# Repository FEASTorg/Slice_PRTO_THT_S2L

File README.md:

# Prototyping Slice

THT components.

BREAD slice for creating new BREAD slices.

## Introduction

[Short introduction on the project.]

## Usage

[Explain how to use the project. Include examples and screenshots if applicable.]

## Documentation

Please refer to the [docs](/docs) for more info.

---

<div align="center">
  
</div>

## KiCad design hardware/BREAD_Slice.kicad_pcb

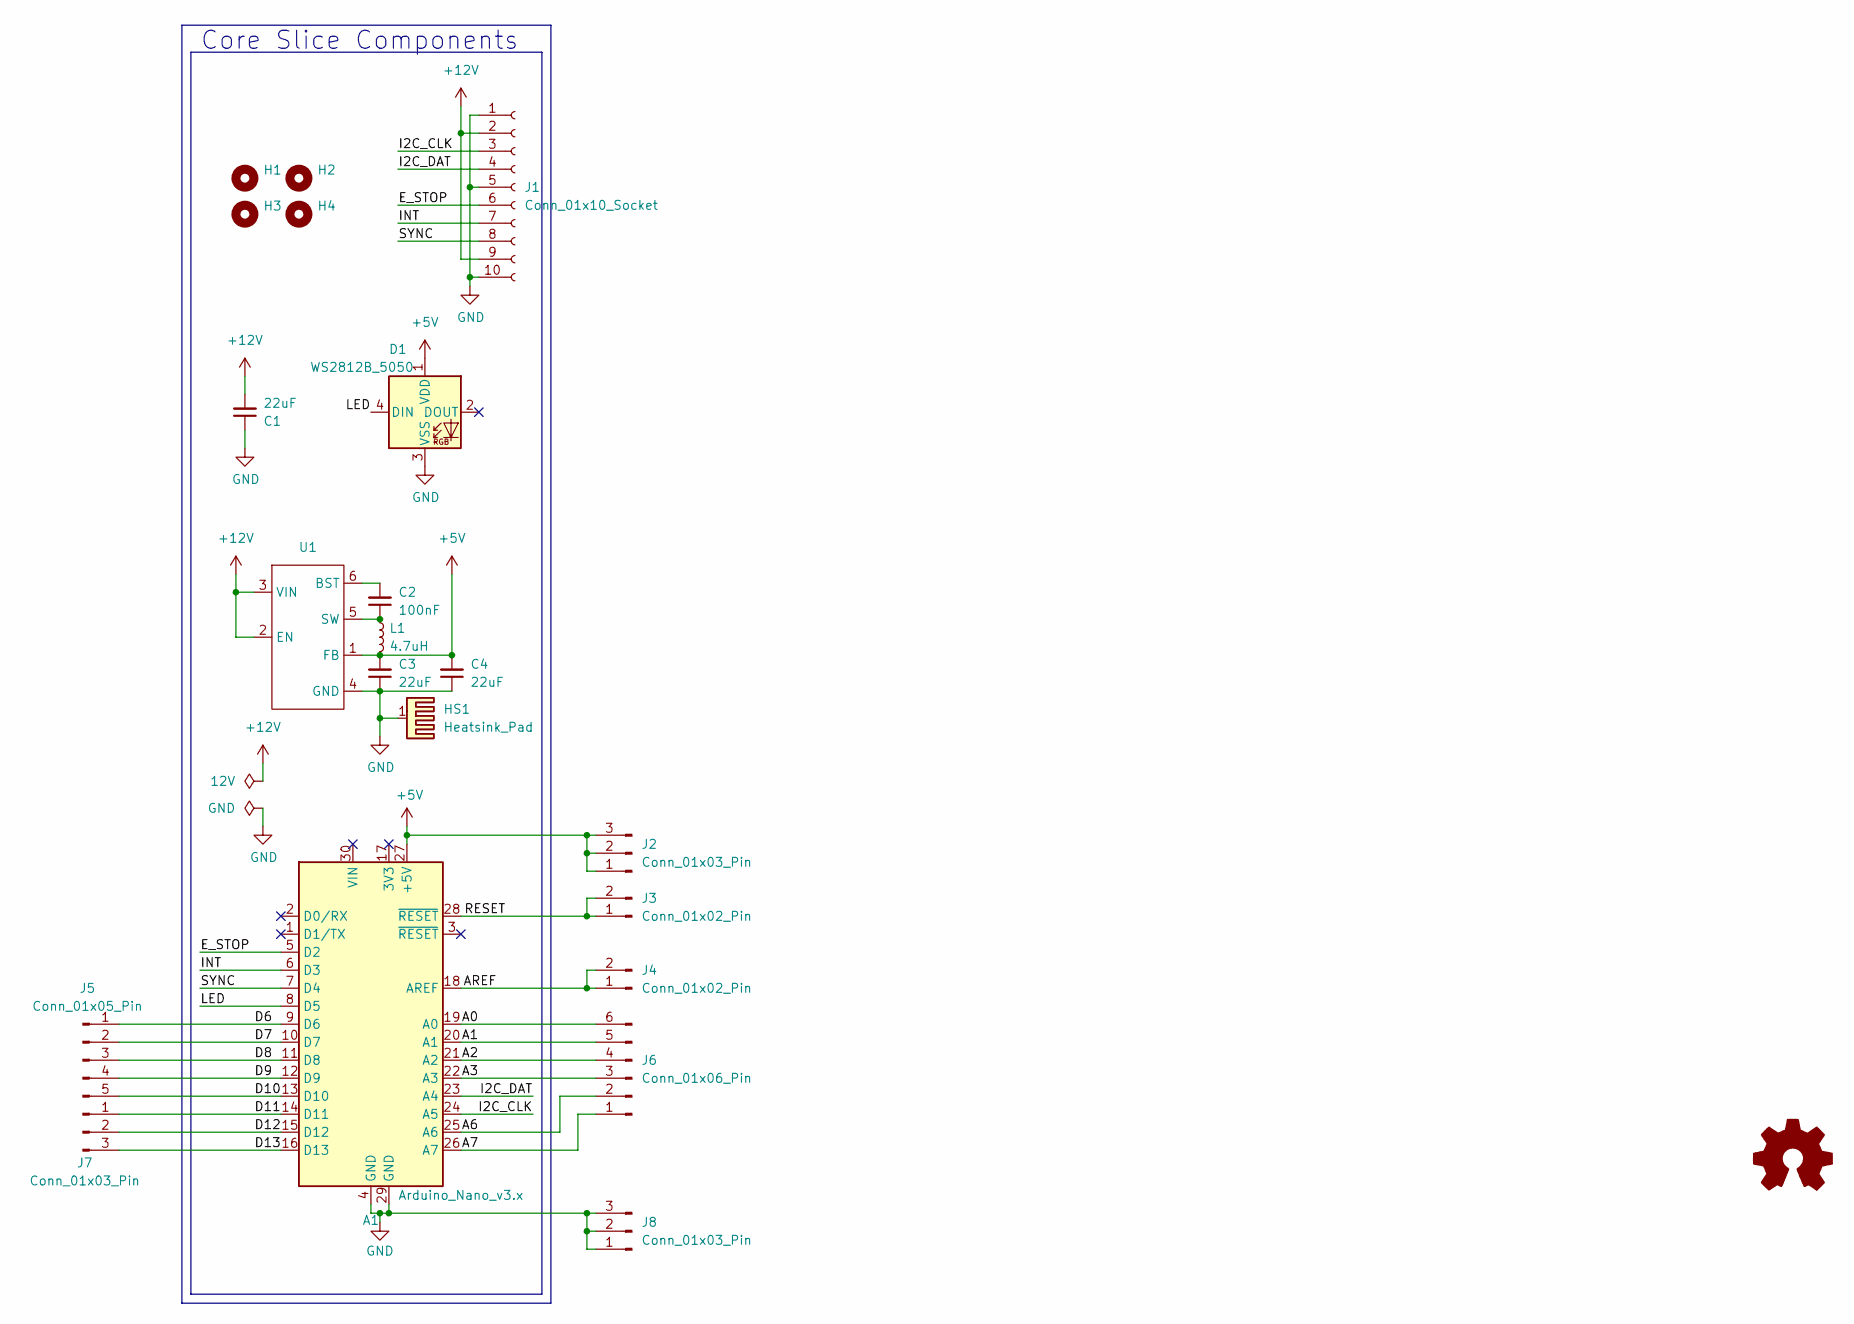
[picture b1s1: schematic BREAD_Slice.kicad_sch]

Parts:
A1: Arduino_Nano_v3.x; Arduino_Nano
C1, C3, C4: 22uF; C_1206_3216Metric
C2: 100nF; C_1206_3216Metric
D1: WS2812B_5050; WS2812-5050-4PIN
H1, H2, H3, H4: MountingHole; MountingHole_5mm
HS1: Heatsink_Pad; Thermal_Pad
J1: Conn_01x10_Socket; PinSocket_1x10_P2.54mm_Horizontal
J2, J7, J8: Conn_01x03_Pin; PinHeader_1x03_P2.54mm_Vertical
J3, J4: Conn_01x02_Pin; PinHeader_1x02_P2.54mm_Vertical
J5: Conn_01x05_Pin; PinHeader_1x05_P2.54mm_Vertical
J6: Conn_01x06_Pin; PinHeader_1x06_P2.54mm_Vertical
L1: 4.7uH; L_1210_3225Metric
U1: TSOT-23-6

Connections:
+5V: A1.27 (+5V), C3.2, C4.2, D1.1 (VDD), J2.1, J2.2, J2.3, L1.2, U1.1 (FB)
+12V: C1.2, J1.2, J1.9, U1.2 (EN), U1.3 (VIN)
/A0: A1.19 (A0), J6.6
/A1: A1.20 (A1), J6.5
/A2: A1.21 (A2), J6.4
/A3: A1.22 (A3), J6.3
/A6: A1.25 (A6), J6.2
/A7: A1.26 (A7), J6.1
/AREF: A1.18 (AREF), J4.1, J4.2
/D6: A1.9 (D6), J5.1
/D7: A1.10 (D7), J5.2
/D8: A1.11 (D8), J5.3
/D9: A1.12 (D9), J5.4
/D10: A1.13 (D10), J5.5
/D11: A1.14 (D11), J7.1
/D12: A1.15 (D12), J7.2
/D13: A1.16 (D13), J7.3
/E_STOP: A1.5 (D2), J1.6
/I2C_CLK: A1.24 (A5), J1.3
/I2C_DAT: A1.23 (A4), J1.4
/INT: A1.6 (D3), J1.7
/LED: A1.8 (D5), D1.4 (DIN)
/RESET: A1.28 (~RESET), J3.1, J3.2
/SYNC: A1.7 (D4), J1.8
GND: A1.4 (GND), A1.29 (GND), C1.1, C3.1, C4.1, D1.3 (VSS), HS1.1, J1.1, J1.5, J1.10, J8.1, J8.2, J8.3, U1.4 (GND)
unnamed: C2.2, U1.6 (BST)
unnamed: C2.1, L1.1, U1.5 (SW)

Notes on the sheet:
Core Slice Components

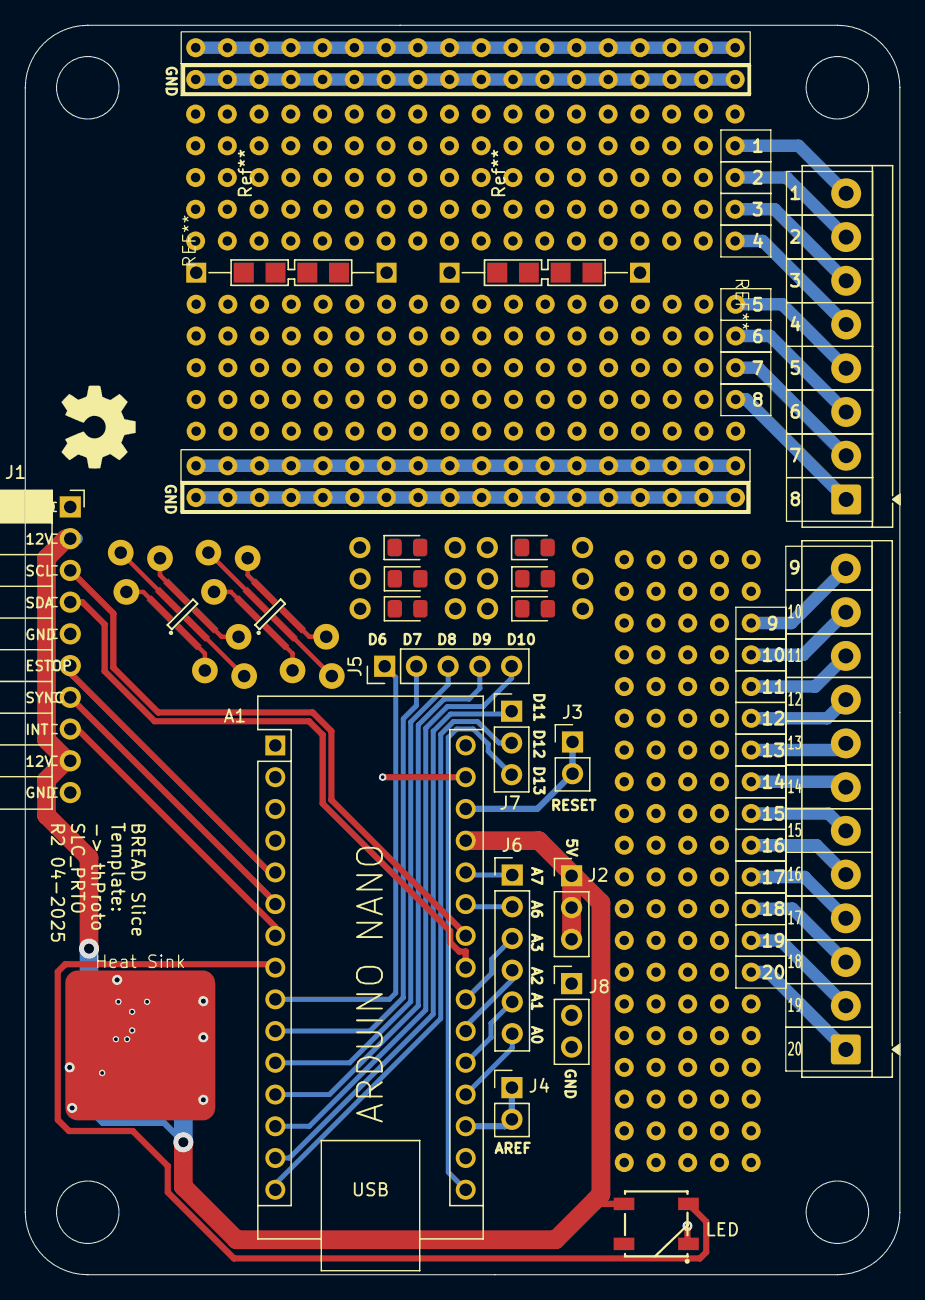
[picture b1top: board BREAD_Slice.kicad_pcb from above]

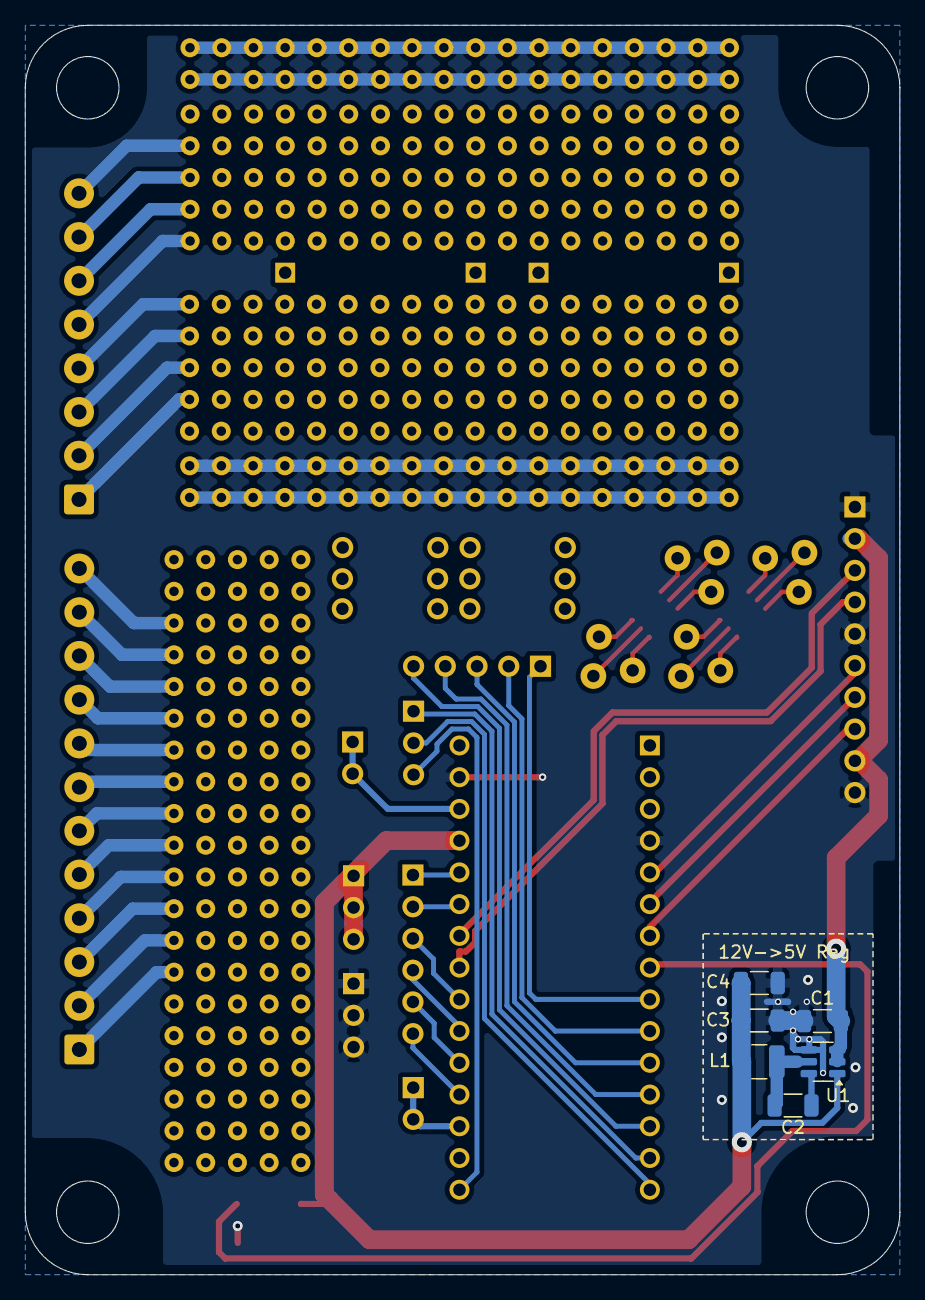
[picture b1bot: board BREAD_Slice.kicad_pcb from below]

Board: 2 copper layers, 70.0 x 100.0 mm, 24 parts (6 on the bottom side), 27 nets.

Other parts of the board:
Logo1: Logo_Open_Hardware_Small; OSHW-Symbol_6.7x6mm_SilkScreen
Ref**: Val**; 1206_HandSolder_Dual_TH_AnnularPad
Ref**#2: Val**; 1206_HandSolder_Dual_TH_AnnularPad

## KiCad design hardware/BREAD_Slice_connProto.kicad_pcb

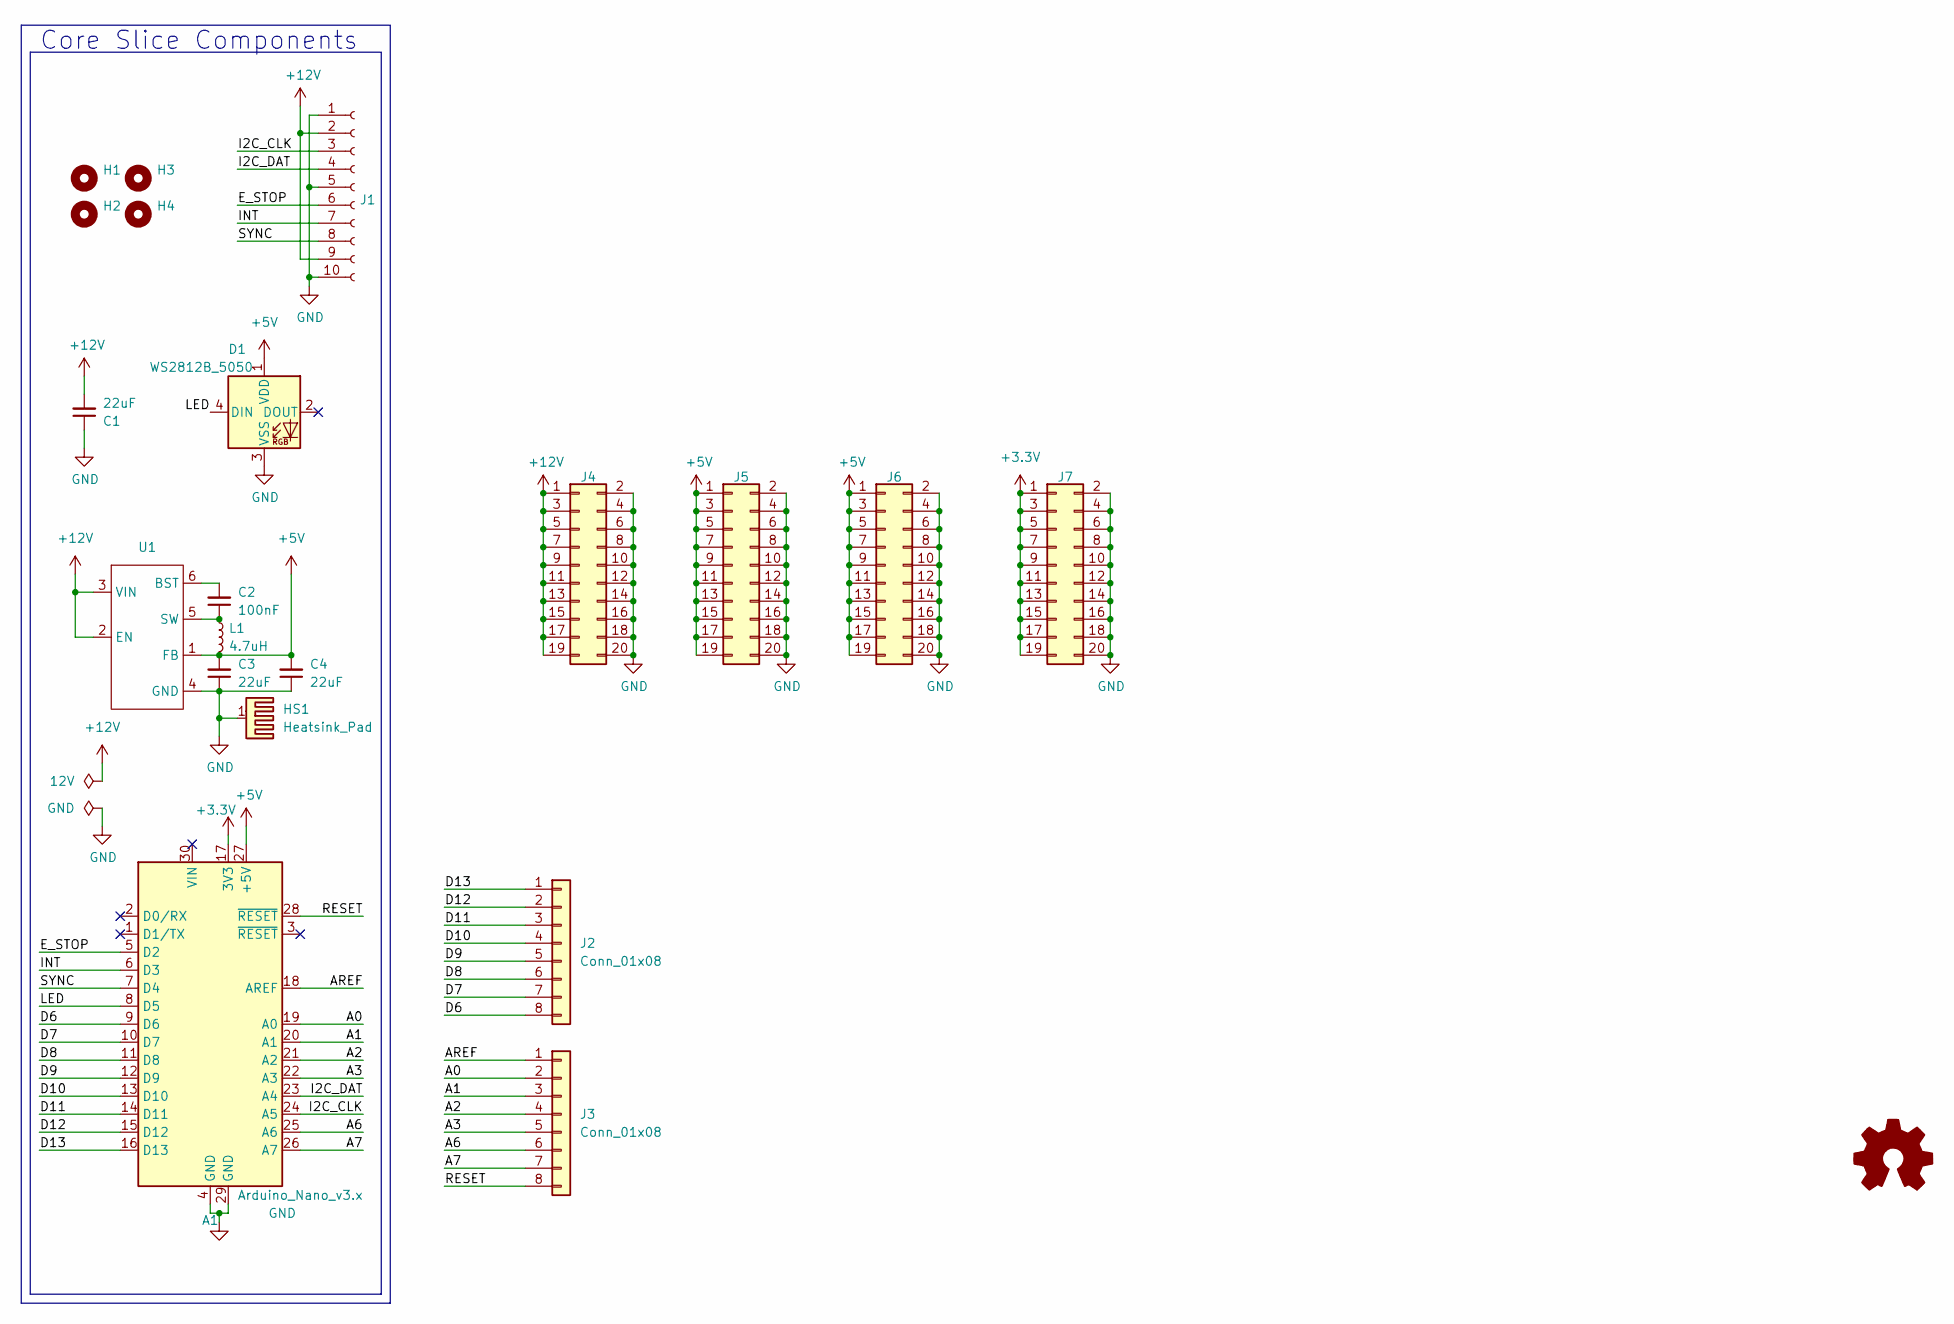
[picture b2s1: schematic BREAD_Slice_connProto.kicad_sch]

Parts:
A1: Arduino_Nano_v3.x; Arduino_Nano
C1, C3, C4: 22uF; C_1206_3216Metric
C2: 100nF; C_1206_3216Metric
D1: WS2812B_5050; WS2812-5050-4PIN
H1, H2, H3, H4: MountingHole; MountingHole_5mm
HS1: Heatsink_Pad; Thermal Pad
J1: Conn_01x10_Female; PinSocket_1x10_P2.54mm_Horizontal
J2, J3: Conn_01x08; TerminalBlock_4Ucon_1x08_P3.50mm_Horizontal
J4, J5, J6, J7: Conn_02x10_Odd_Even; PinHeader_2x10_P2.54mm_Vertical
L1: 4.7uH; L_1210_3225Metric
U1: TSOT-23-6

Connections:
+3.3V: A1.17 (3V3), J7.1, J7.3, J7.5, J7.7, J7.9, J7.11, J7.13, J7.15, J7.17, J7.19
+5V: A1.27 (+5V), C3.2, C4.2, D1.1 (VDD), J5.1, J5.3, J5.5, J5.7, J5.9, J5.11, J5.13, J5.15, J5.17, J5.19, J6.1, J6.3, J6.5, J6.7, J6.9, J6.11, J6.13, J6.15, J6.17, J6.19, L1.2, U1.1 (FB)
+12V: C1.2, J1.2, J1.9, J4.1, J4.3, J4.5, J4.7, J4.9, J4.11, J4.13, J4.15, J4.17, J4.19, U1.2 (EN), U1.3 (VIN)
/A0: A1.19 (A0), J3.2
/A1: A1.20 (A1), J3.3
/A2: A1.21 (A2), J3.4
/A3: A1.22 (A3), J3.5
/A6: A1.25 (A6), J3.6
/A7: A1.26 (A7), J3.7
/AREF: A1.18 (AREF), J3.1
/D6: A1.9 (D6), J2.8
/D7: A1.10 (D7), J2.7
/D8: A1.11 (D8), J2.6
/D9: A1.12 (D9), J2.5
/D10: A1.13 (D10), J2.4
/D11: A1.14 (D11), J2.3
/D12: A1.15 (D12), J2.2
/D13: A1.16 (D13), J2.1
/E_STOP: A1.5 (D2), J1.6
/I2C_CLK: A1.24 (A5), J1.3
/I2C_DAT: A1.23 (A4), J1.4
/INT: A1.6 (D3), J1.7
/LED: A1.8 (D5), D1.4 (DIN)
/RESET: A1.28 (~RESET), J3.8
/SYNC: A1.7 (D4), J1.8
GND: A1.4 (GND), A1.29 (GND), C1.1, C3.1, C4.1, D1.3 (VSS), HS1.1, J1.1, J1.5, J1.10, J4.2, J4.4, J4.6, J4.8, J4.10, J4.12, J4.14, J4.16, J4.18, J4.20, J5.2, J5.4, J5.6, J5.8, J5.10, J5.12, J5.14, J5.16, J5.18, J5.20, J6.2, J6.4, J6.6, J6.8, J6.10, J6.12, J6.14, J6.16, J6.18, J6.20, J7.2, J7.4, J7.6, J7.8, J7.10, J7.12, J7.14, J7.16, J7.18, J7.20, U1.4 (GND)
unnamed: C2.2, U1.6 (BST)
unnamed: C2.1, L1.1, U1.5 (SW)

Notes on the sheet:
Core Slice Components

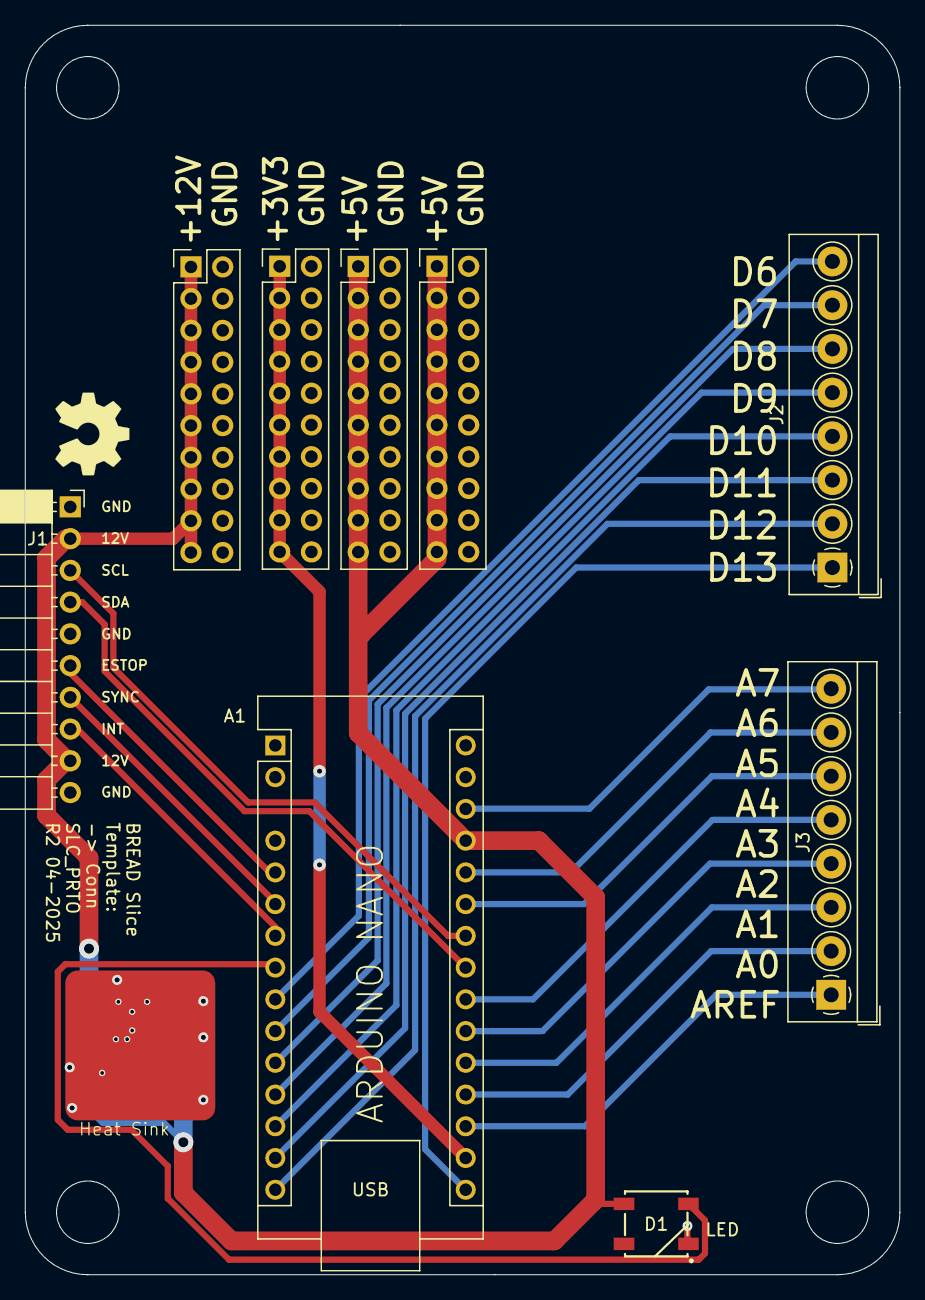
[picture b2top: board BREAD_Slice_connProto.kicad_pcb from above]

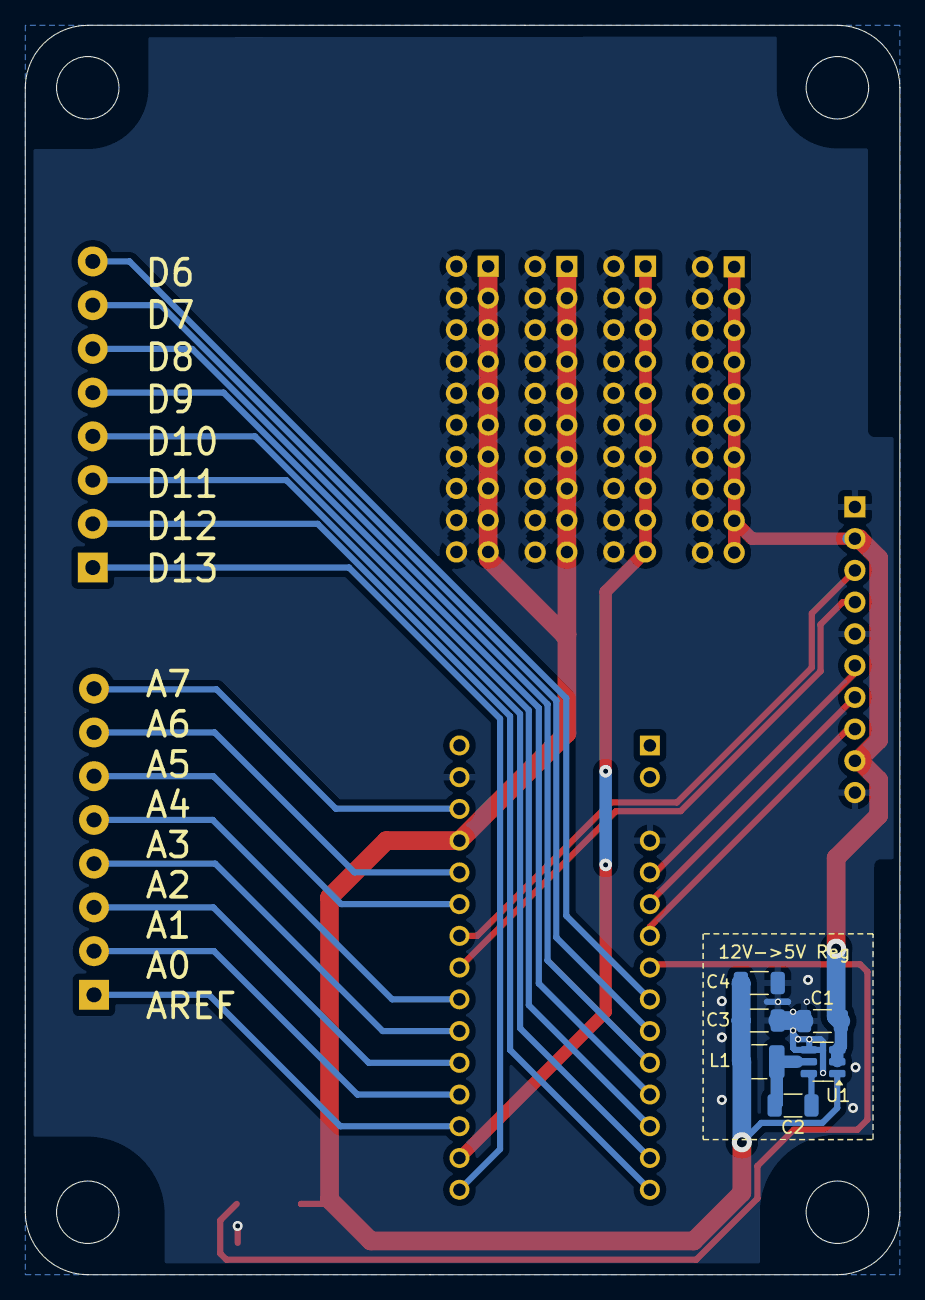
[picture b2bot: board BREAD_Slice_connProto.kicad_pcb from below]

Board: 2 copper layers, 70.0 x 100.0 mm, 21 parts (6 on the bottom side), 28 nets.

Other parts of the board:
Logo1: Logo_Open_Hardware_Small; OSHW-Symbol_6.7x6mm_SilkScreen

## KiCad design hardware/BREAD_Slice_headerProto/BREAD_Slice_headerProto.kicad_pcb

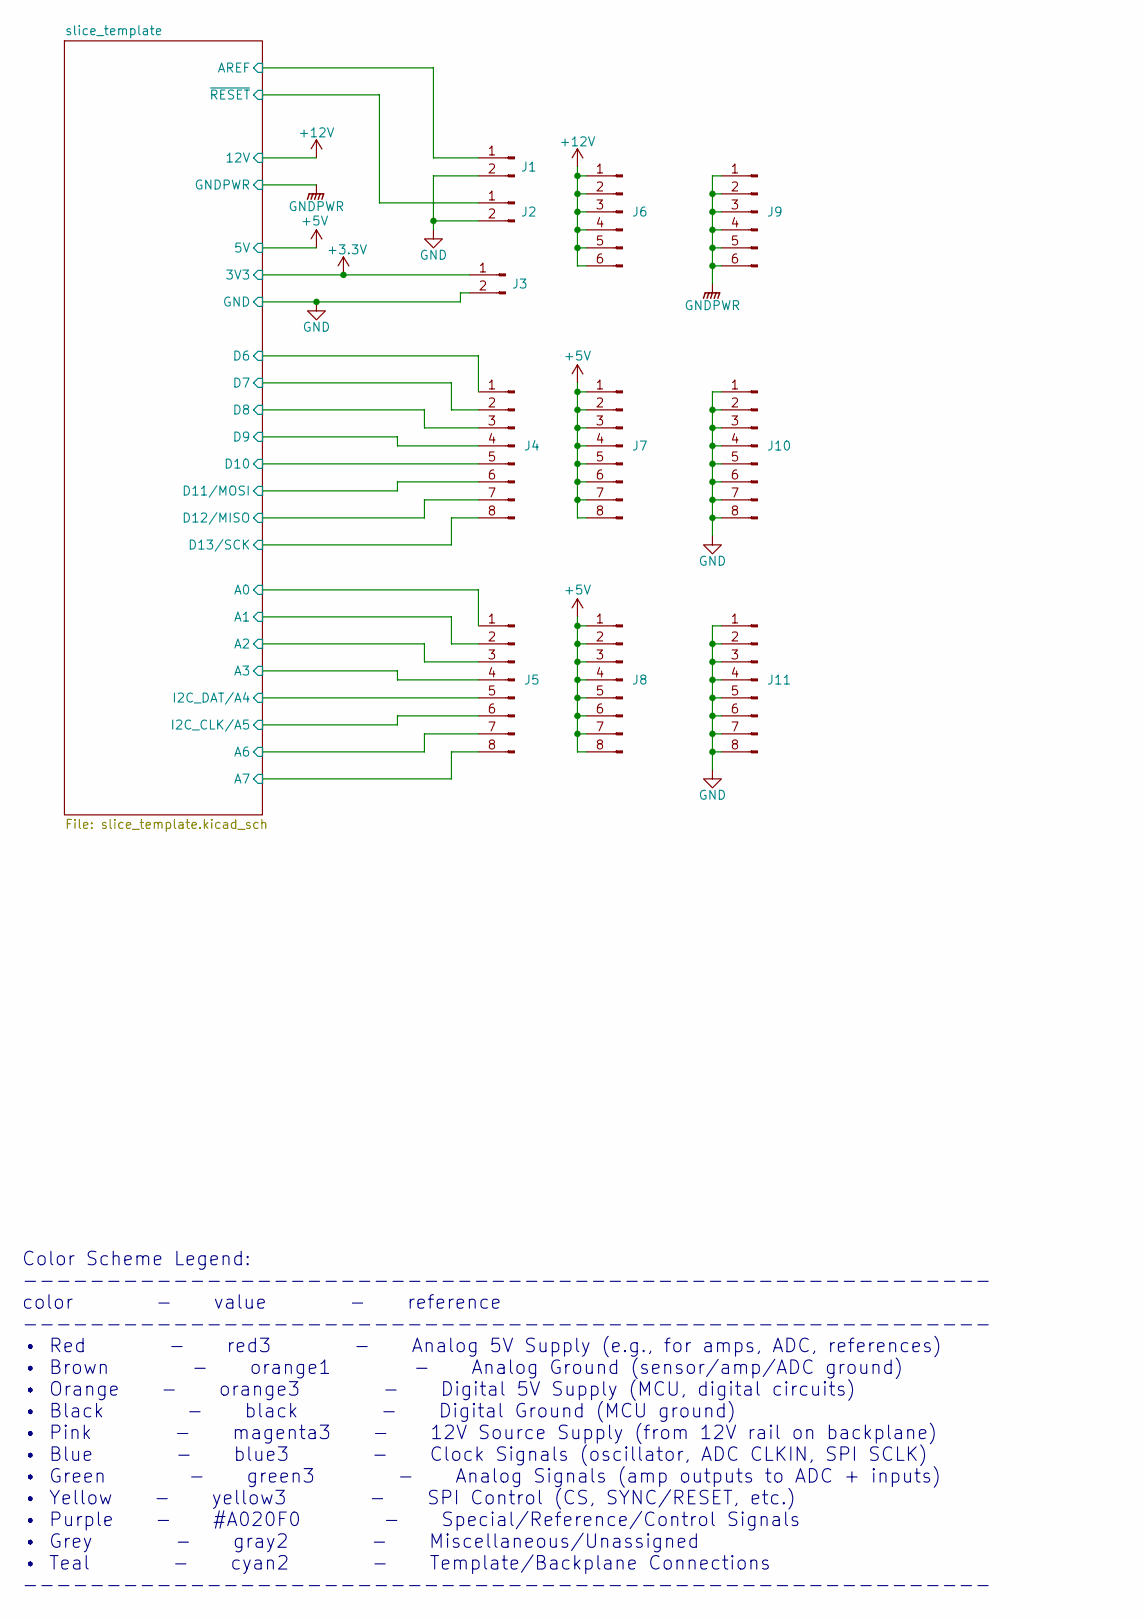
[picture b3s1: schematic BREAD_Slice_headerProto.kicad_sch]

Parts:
J1, J2, J3: Conn_01x02_Pin; PinHeader_1x02_P2.54mm_Vertical
J4, J5, J7, J8, J10, J11: Conn_01x08_Pin; PinHeader_1x08_P2.54mm_Vertical
J6, J9: Conn_01x06_Pin; PinHeader_1x06_P2.54mm_Vertical

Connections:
+3.3V: J3.1; also elsewhere on the board
+5V: J7.1, J7.2, J7.3, J7.4, J7.5, J7.6, J7.7, J7.8, J8.1, J8.2, J8.3, J8.4, J8.5, J8.6, J8.7, J8.8; also elsewhere on the board
+12V: J6.1, J6.2, J6.3, J6.4, J6.5, J6.6; also elsewhere on the board
/slice_template/A0: J5.1; also elsewhere on the board
/slice_template/A1: J5.2; also elsewhere on the board
/slice_template/A2: J5.3; also elsewhere on the board
/slice_template/A3: J5.4; also elsewhere on the board
/slice_template/A6: J5.7; also elsewhere on the board
/slice_template/A7: J5.8; also elsewhere on the board
/slice_template/AREF: J1.1; also elsewhere on the board
/slice_template/D6: J4.1; also elsewhere on the board
/slice_template/D7: J4.2; also elsewhere on the board
/slice_template/D8: J4.3; also elsewhere on the board
/slice_template/D9: J4.4; also elsewhere on the board
/slice_template/D10: J4.5; also elsewhere on the board
/slice_template/D11/MOSI: J4.6; also elsewhere on the board
/slice_template/D12/MISO: J4.7; also elsewhere on the board
/slice_template/D13/SCK: J4.8; also elsewhere on the board
/slice_template/I2C_CLK/A5: J5.6; also elsewhere on the board
/slice_template/I2C_DAT/A4: J5.5; also elsewhere on the board
/slice_template/~RESET: J2.1; also elsewhere on the board
GND: J1.2, J2.2, J3.2, J10.1, J10.2, J10.3, J10.4, J10.5, J10.6, J10.7, J10.8, J11.1, J11.2, J11.3, J11.4, J11.5, J11.6, J11.7, J11.8; also elsewhere on the board
GNDPWR: J9.1, J9.2, J9.3, J9.4, J9.5, J9.6; also elsewhere on the board

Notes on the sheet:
Color Scheme Legend: ---------------------------------------------------------- color - value - reference ---------------------------------------------------------- • Red - red3 - Analog 5V Supply (e.g., for amps, ADC, references) • Brown - orange1 - Analog Ground (sensor/amp/ADC ground) • Orange -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

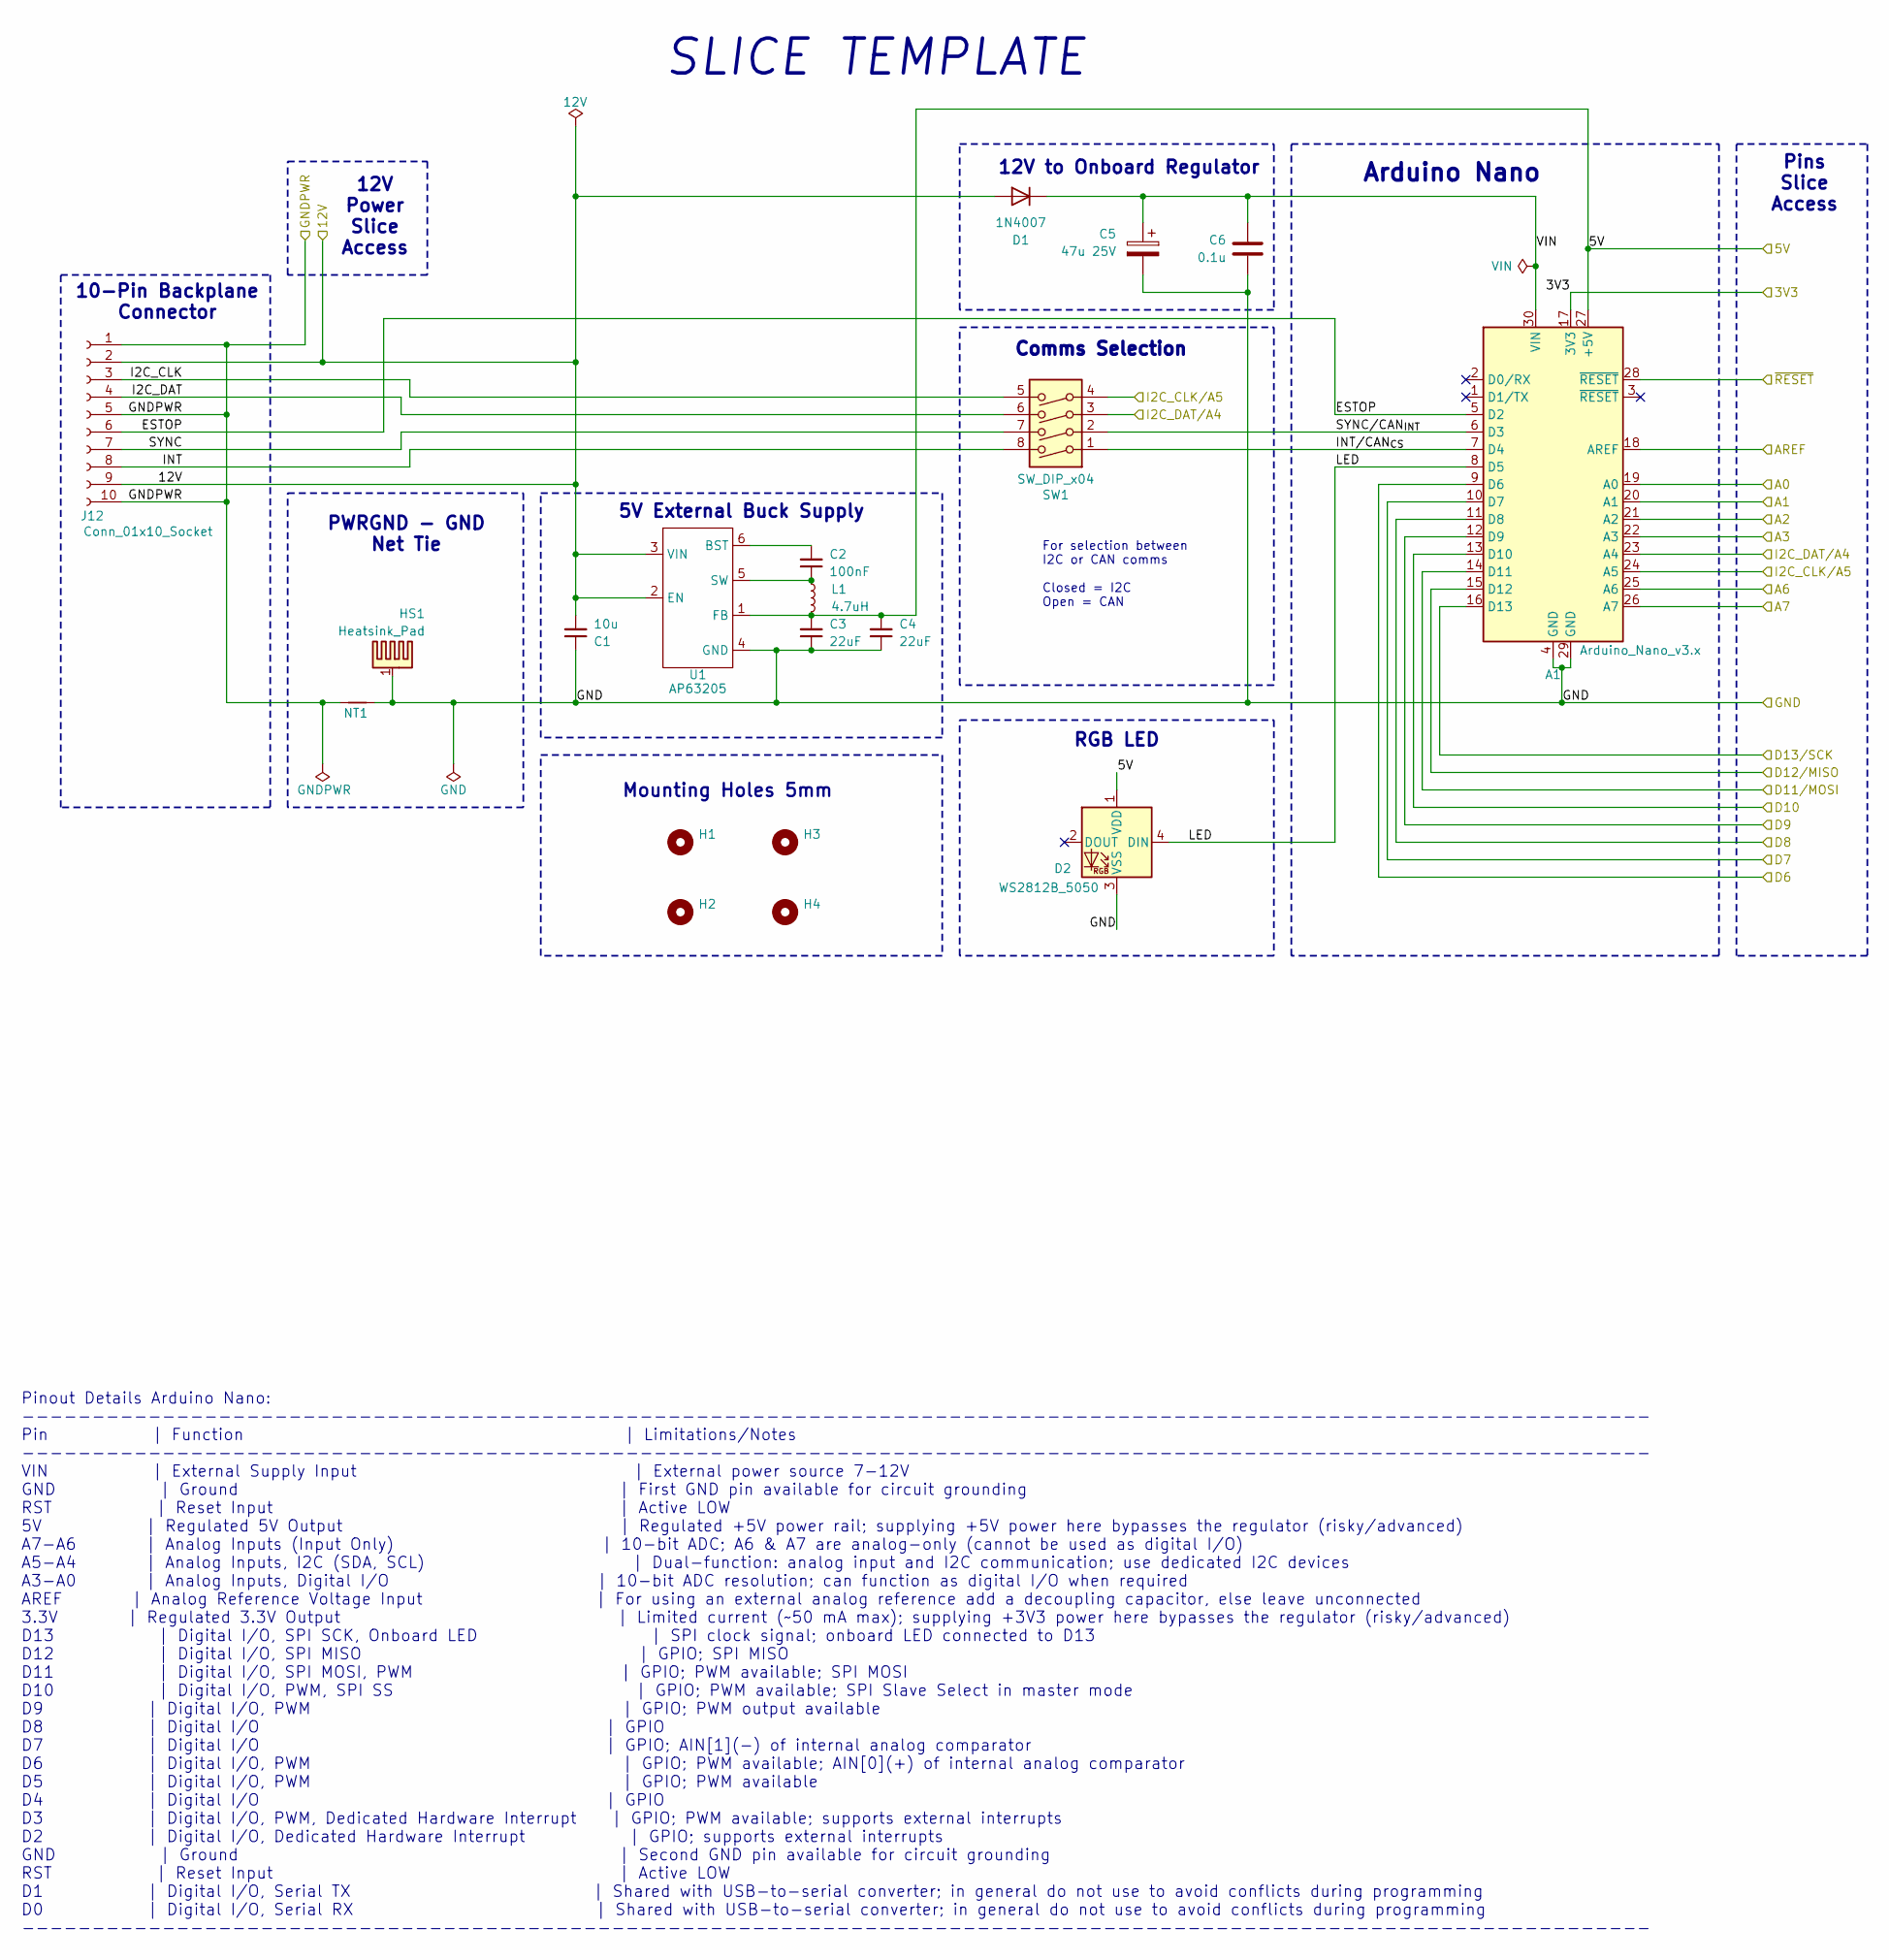
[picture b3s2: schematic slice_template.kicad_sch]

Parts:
A1: Arduino_Nano_v3.x; Arduino_Nano_Headers
C1: 10u; C_1206_3216Metric
C2: 100nF; C_1206_3216Metric
C3, C4: 22uF; C_1206_3216Metric
C5: 47u 25V; CP_Elec_6.3x7.7
C6: 0.1u; C_0805_2012Metric_Pad1.18x1.45mm_HandSolder
D1: 1N4007; D_SOD-123F
D2: WS2812B_5050; WS2812-5050-4PIN
H1, H2, H3, H4: MountingHole; MountingHole_5mm
HS1: Heatsink_Pad; Thermal Pad
J12: Conn_01x10_Socket; PinSocket_1x10_P2.54mm_Horizontal
L1: 4.7uH; L_1210_3225Metric
NT1: NetTie_2; NetTie-2_SMD_Pad2.0mm
SW1: SW_DIP_x04; SW_DIP_SPSTx04_Slide_9.78x12.34mm_W8.61mm_P2.54mm
U1: AP63205; SOIC_05WU-7_DIO-M

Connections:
+3.3V: A1.17 (3V3); also elsewhere on the board
+5V: A1.27 (+5V), C3.2, C4.2, D2.1 (VDD), L1.2, U1.1 (FB); also elsewhere on the board
+12V: C1.2, D1.2 (A), J12.2, J12.9, U1.2 (EN), U1.3 (VIN); also elsewhere on the board
/slice_template/A0: A1.19 (A0); also elsewhere on the board
/slice_template/A1: A1.20 (A1); also elsewhere on the board
/slice_template/A2: A1.21 (A2); also elsewhere on the board
/slice_template/A3: A1.22 (A3); also elsewhere on the board
/slice_template/A6: A1.25 (A6); also elsewhere on the board
/slice_template/A7: A1.26 (A7); also elsewhere on the board
/slice_template/AREF: A1.18 (AREF); also elsewhere on the board
/slice_template/D6: A1.9 (D6); also elsewhere on the board
/slice_template/D7: A1.10 (D7); also elsewhere on the board
/slice_template/D8: A1.11 (D8); also elsewhere on the board
/slice_template/D9: A1.12 (D9); also elsewhere on the board
/slice_template/D10: A1.13 (D10); also elsewhere on the board
/slice_template/D11/MOSI: A1.14 (D11); also elsewhere on the board
/slice_template/D12/MISO: A1.15 (D12); also elsewhere on the board
/slice_template/D13/SCK: A1.16 (D13); also elsewhere on the board
/slice_template/ESTOP: A1.5 (D2), J12.6
/slice_template/I2C_CLK: J12.3, SW1.5
/slice_template/I2C_CLK/A5: A1.24 (A5), SW1.4; also elsewhere on the board
/slice_template/I2C_DAT: J12.4, SW1.6
/slice_template/I2C_DAT/A4: A1.23 (A4), SW1.3; also elsewhere on the board
/slice_template/INT: J12.8, SW1.8
/slice_template/INT/CAN_{CS}: A1.7 (D4), SW1.1
/slice_template/LED: A1.8 (D5), D2.4 (DIN)
/slice_template/SYNC: J12.7, SW1.7
/slice_template/SYNC/CAN_{INT}: A1.6 (D3), SW1.2
/slice_template/VIN: A1.30 (VIN), C5.1, C6.1, D1.1 (K)
/slice_template/~RESET: A1.28 (~RESET); also elsewhere on the board
GND: A1.4 (GND), A1.29 (GND), C1.1, C3.1, C4.1, C5.2, C6.2, D2.3 (VSS), HS1.1, NT1.1, U1.4 (GND); also elsewhere on the board
GNDPWR: J12.1, J12.5, J12.10, NT1.2; also elsewhere on the board
unnamed: C2.2, U1.6 (BST)
unnamed: C2.1, L1.1, U1.5 (SW)

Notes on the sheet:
Pins Slice Access
10-Pin Backplane Connector
PWRGND - GND Net Tie
SLICE TEMPLATE
RGB LED
Pinout Details Arduino Nano: -------------------------------------------------------------------------------------------------------------------- Pin | Function | Limitations/Notes -------------------------------------------------------------------------------------------------------------------- V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
Comms Selection
Mounting Holes 5mm
12V Power Slice Access
For selection between I2C or CAN comms Closed = I2C Open = CAN
Arduino Nano
12V to Onboard Regulator
5V External Buck Supply
